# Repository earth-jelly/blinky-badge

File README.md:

# blinky-badge
This is a blinky board with an original graphic of Heidi the raccoon (and her braincells working hard to spark an 'Aha moment') on it.

## Why?
When I first started this project, I envisioned this blinky board to be used as a light up badge for my (former) FRC team. However, as I was getting everything set up, I realized that I wanted this project to be something that I can be proud of and actually like, so I changed the overall theme to what I like, which is Heidi. 

I ultimately decided on the Aha! moment Heidi as my design because the nature of the blinky board (the fact that it lights up) reminded me of an lightbulb and an realization moment. This, as you can tell in the final product, translated directly to the silkscreen art on the board.

## Schematic + Silkscreen + PCB

## So, what did I learn?
As a person who have tried making a PCB before, making the schematics and routing the components weren't anything new. However, importing footprints from online library, ordering the PCB, and creating a BOM were something that was completely new to me and that I had to learn (albeit, it took a little too long to do).

## Cost Estimate

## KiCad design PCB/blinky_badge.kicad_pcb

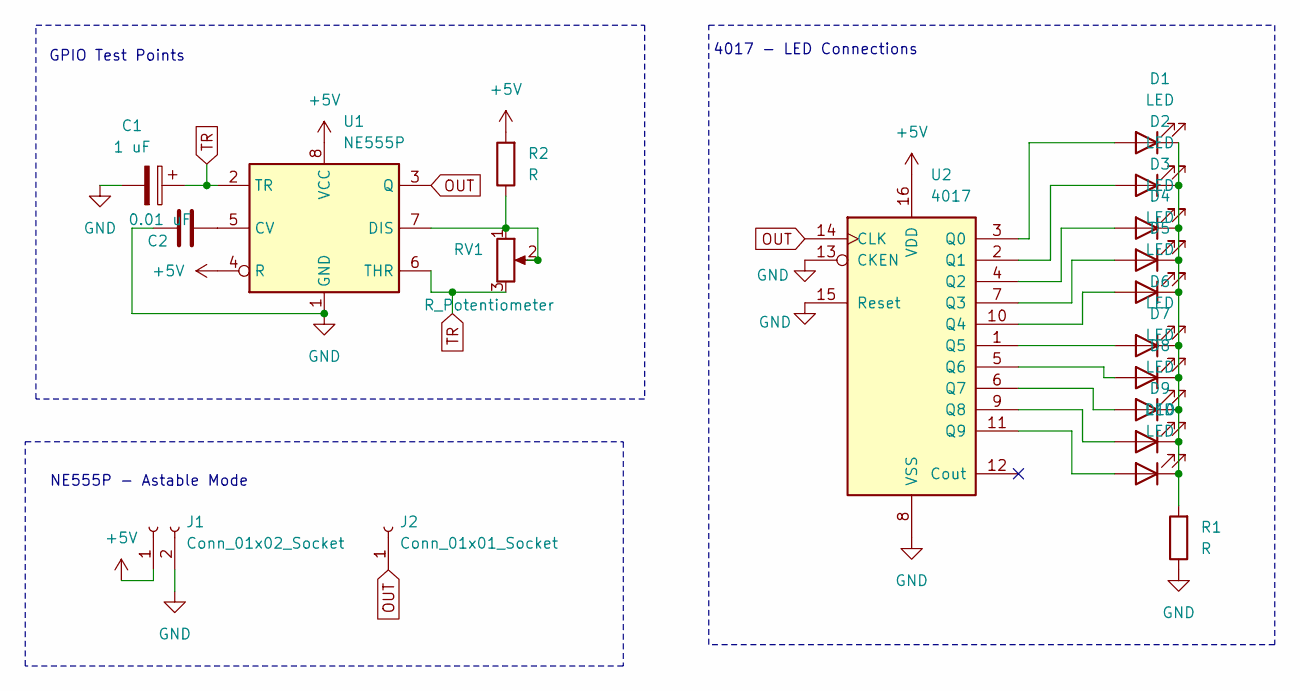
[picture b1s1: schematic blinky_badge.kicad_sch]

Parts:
C1: 1 uF; CP_Radial_D5.0mm_P2.00mm
C2: 0.01 uF; C_Disc_D7.5mm_W2.5mm_P5.00mm
D1, D2, D3, D4, D5, D6, D7, D8, D9, D10: LED; LED_D3.0mm
J1: Conn_01x02_Socket; PinHeader_1x02_P2.54mm_Vertical
J2: Conn_01x01_Socket; PinHeader_1x01_P2.54mm_Vertical
R1, R2: R; R_Axial_DIN0207_L6.3mm_D2.5mm_P7.62mm_Horizontal
RV1: R_Potentiometer; Potentiometer_Vishay_T93YA_Vertical
U1: NE555P; DIP-8_W7.62mm
U2: 4017; N16

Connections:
+5V: J1.1, R2.2, U1.4 (R), U1.8 (VCC), U2.16 (VDD)
GND: C1.2, C2.1, J1.2, R1.1, U1.1 (GND), U2.8 (VSS), U2.13 (CKEN), U2.15 (Reset)
unnamed: D1.2 (A), U2.3 (Q0)
unnamed: D1.1 (K), D2.1 (K), D3.1 (K), D4.1 (K), D5.1 (K), D6.1 (K), D7.1 (K), D8.1 (K), D9.1 (K), D10.1 (K), R1.2
unnamed: D2.2 (A), U2.2 (Q1)
unnamed: D3.2 (A), U2.4 (Q2)
unnamed: D4.2 (A), U2.7 (Q3)
unnamed: D5.2 (A), U2.10 (Q4)
unnamed: D6.2 (A), U2.1 (Q5)
unnamed: D7.2 (A), U2.5 (Q6)
unnamed: D8.2 (A), U2.6 (Q7)
unnamed: D9.2 (A), U2.9 (Q8)
unnamed: D10.2 (A), U2.11 (Q9)
unnamed: C2.2, U1.5 (CV)
unnamed: R2.1, RV1.1, RV1.2, U1.7 (DIS)
OUT: J2.1, U1.3 (Q), U2.14 (CLK)
TR: C1.1, RV1.3, U1.2 (TR), U1.6 (THR)

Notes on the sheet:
GPIO Test Points
NE555P - Astable Mode
4017 - LED Connections

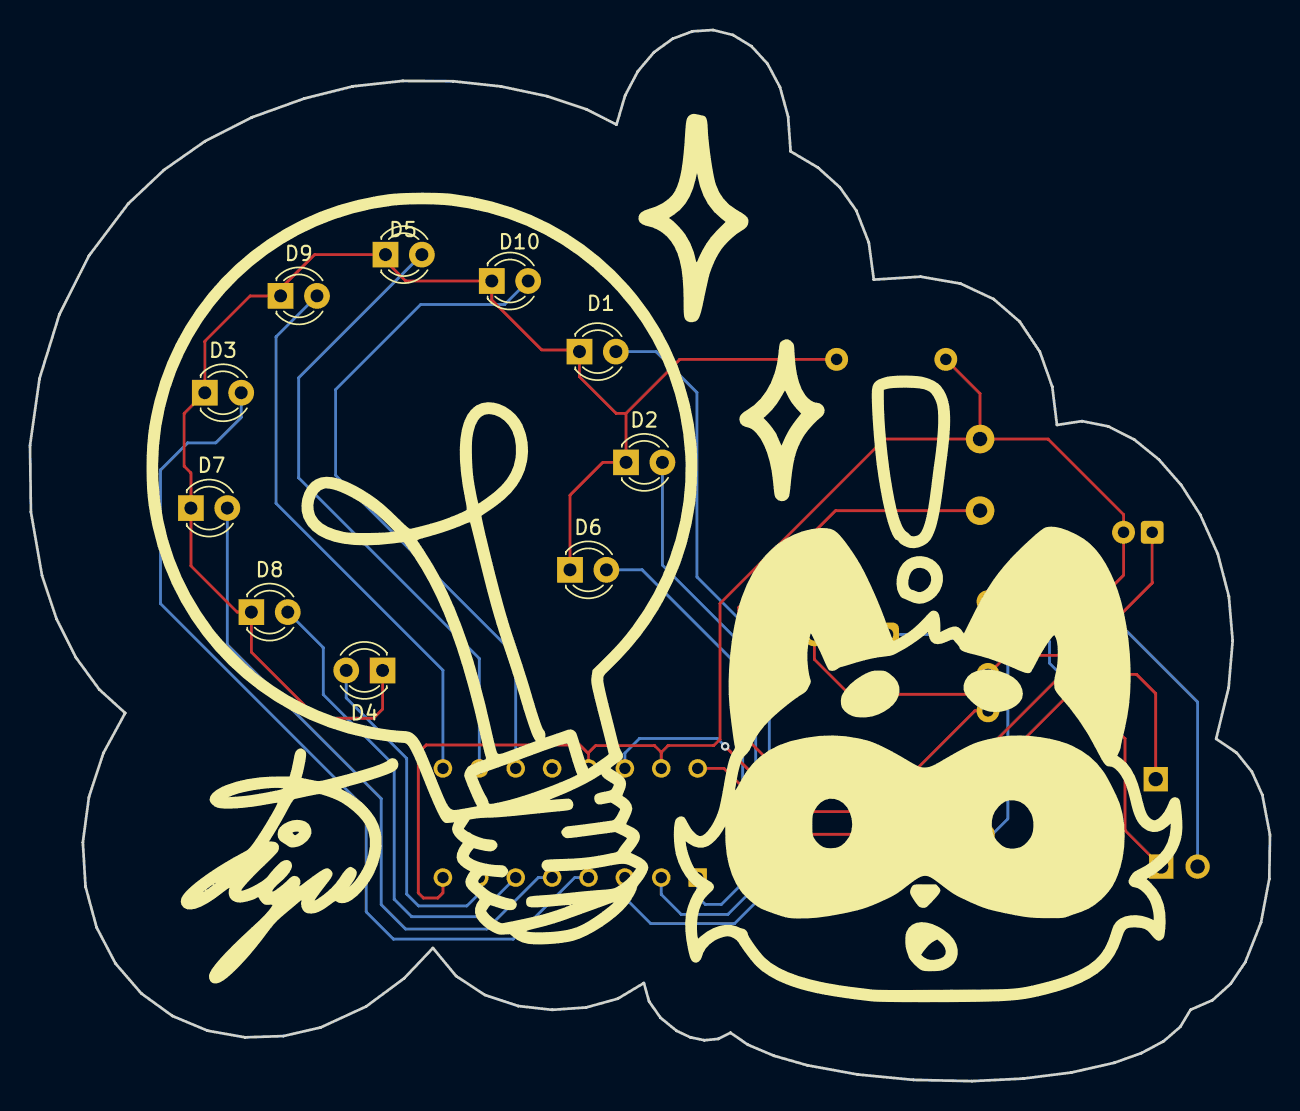
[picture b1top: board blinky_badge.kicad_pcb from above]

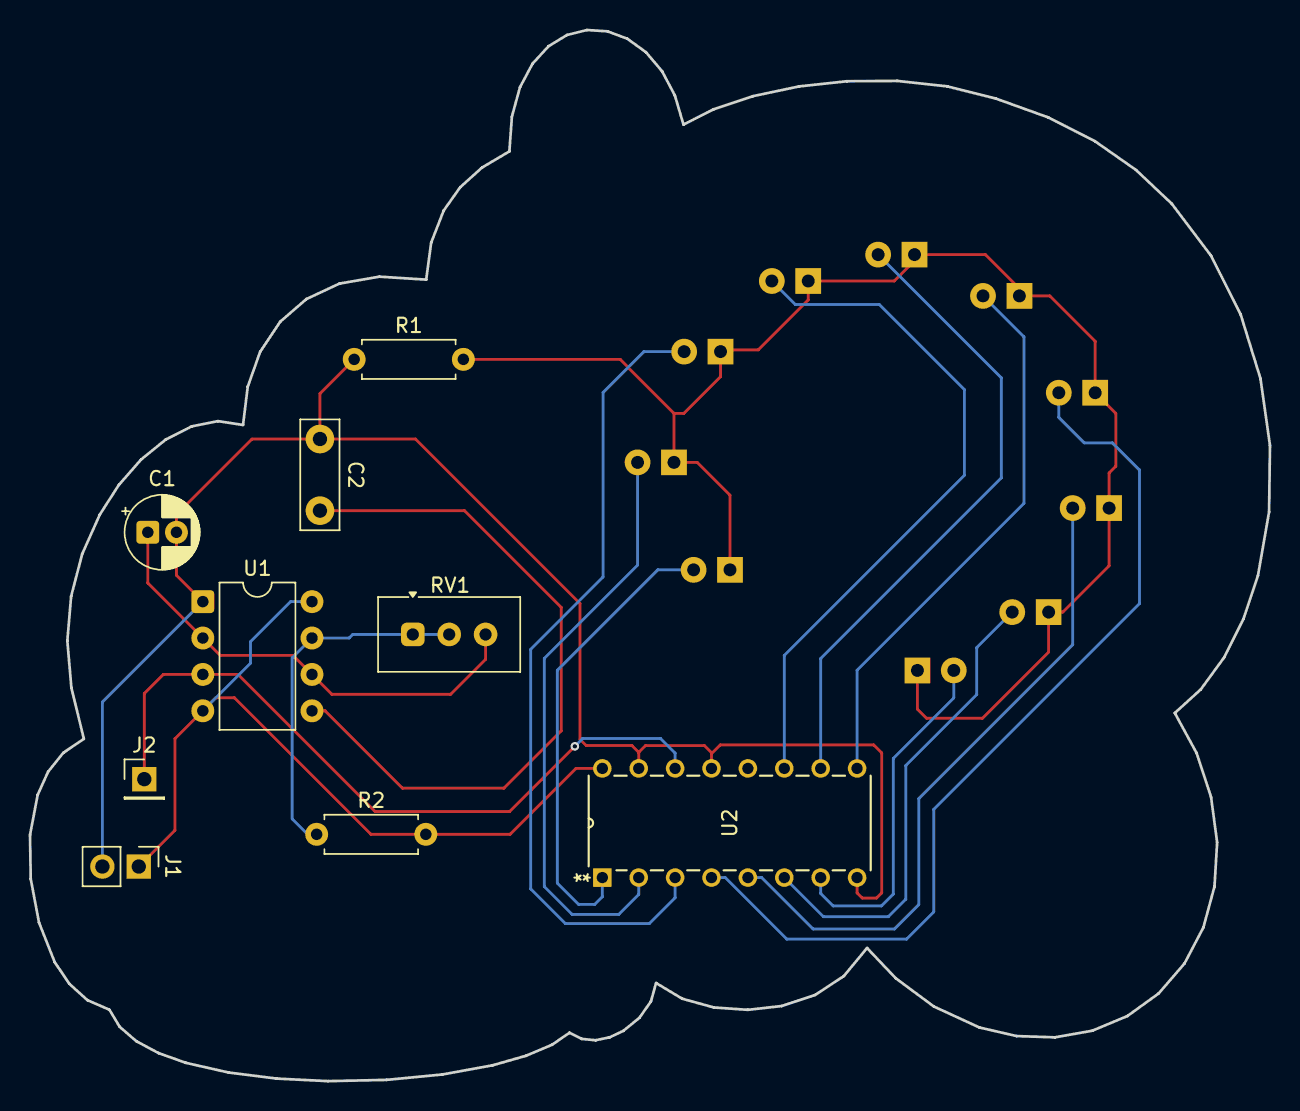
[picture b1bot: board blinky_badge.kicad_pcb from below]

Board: 2 copper layers, 86.5 x 73.4 mm, 19 parts (9 on the bottom side), 17 nets.

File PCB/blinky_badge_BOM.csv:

"Reference","Qty","Value","DNP","Exclude from BOM","Exclude from Board","Footprint","Datasheet"
"C1","1","1 uF","","","","Capacitor_THT:CP_Radial_D5.0mm_P2.00mm","~"
"C2","1","0.01 uF","","","","Capacitor_THT:C_Disc_D7.5mm_W2.5mm_P5.00mm","~"
"D1,D2,D3,D4,D5,D6,D7,D8,D9,D10","10","LED","","","","LED_THT:LED_D3.0mm","~"
"J1","1","Conn_01x02_Socket","","","","Connector_PinHeader_2.54mm:PinHeader_1x02_P2.54mm_Vertical","~"
"J2","1","Conn_01x01_Socket","","","","Connector_PinHeader_2.54mm:PinHeader_1x01_P2.54mm_Vertical","~"
"R1,R2","2","R","","","","Resistor_THT:R_Axial_DIN0207_L6.3mm_D2.5mm_P7.62mm_Horizontal","~"
"RV1","1","R_Potentiometer","","","","Potentiometer_THT:Potentiometer_Vishay_T93YA_Vertical","~"
"U1","1","NE555P","","","","Package_DIP:DIP-8_W7.62mm","http://www.ti.com/lit/ds/symlink/ne555.pdf"
"U2","1","4017","","","","CD4017:N16","http://www.intersil.com/content/dam/Intersil/documents/cd40/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"

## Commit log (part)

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2026-06-06 Local work update
2026-06-06 Gerber file update
